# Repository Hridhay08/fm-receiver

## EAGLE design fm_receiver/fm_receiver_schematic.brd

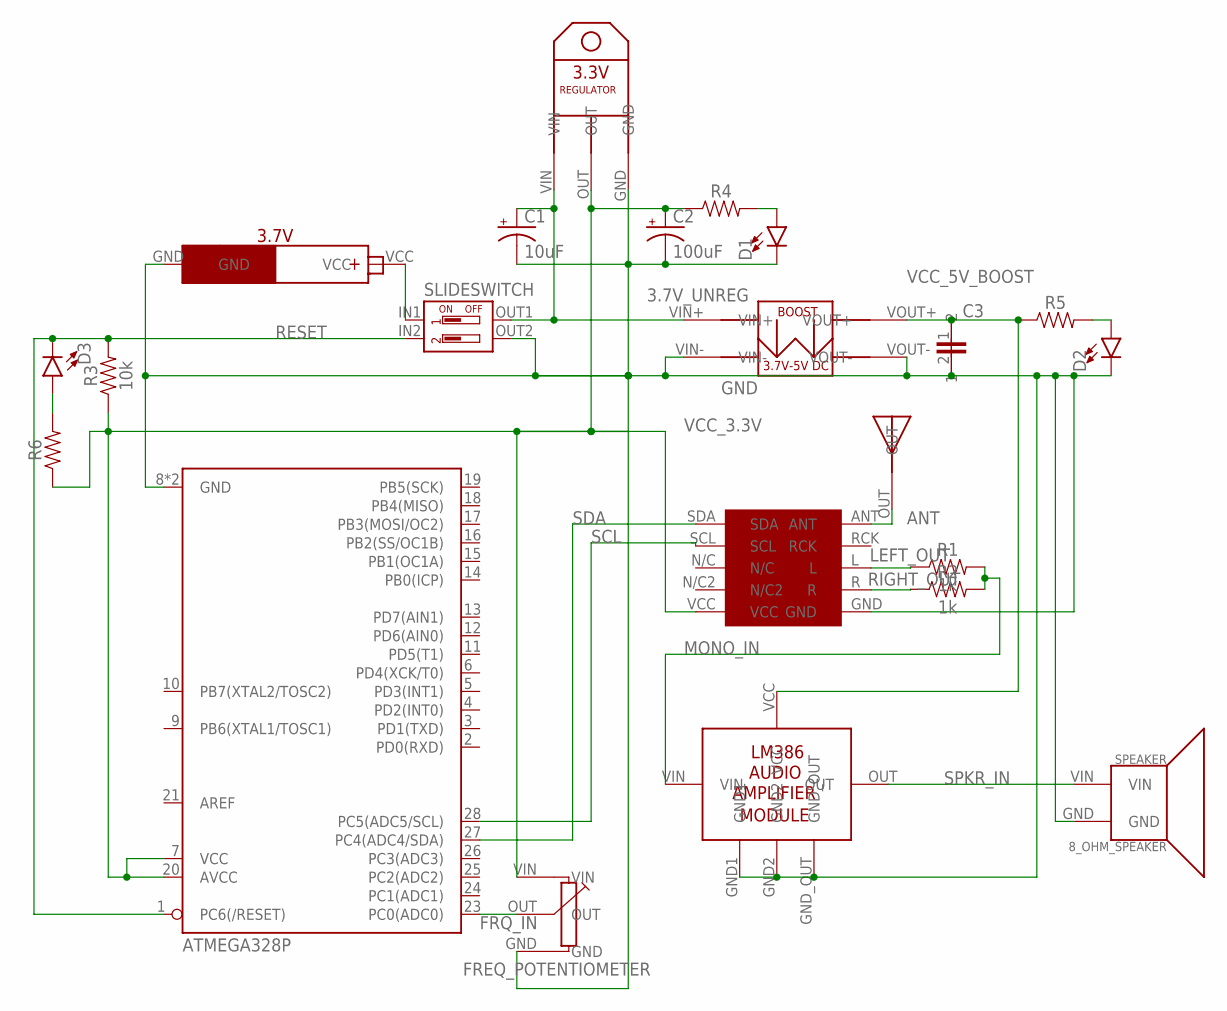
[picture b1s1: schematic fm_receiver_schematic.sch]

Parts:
3.3V_REGULATOR: LDO_REG_3.3V
3.7_5_BOOST: 3.7V_5V_BOOST_CONV
ANTENNA: SIMPLE_ANTENNA
ATMEGA328P: 328P; DIP28
C1: 10uF; CPOL-RADIAL-2.5MM-5MM
C2: 100uF; CPOL-RADIAL-2.5MM-6.5MM
C3: 0.1UF_CER_CAP
D1, D2, D3: LED5MM; LED_5MM
FM_RECEIVER: RDA
FREQ_POTENTIOMETER: POTENTIOMETER_LARGE
LM386_MODULE: LM386_AUDIO_AMP_MODULE
PWR_SUPPLY: 3.7V_PWR_DESIGNATOR
R1, R2: 1k; AXIAL-0.3
R3: 10k; AXIAL-0.3
R4, R5, R6: AXIAL-0.3
SLIDESWITCH: 2_WAY_DIP_PWR_RST_SLIDESWITCH
SPEAKER: 8_OHM_SPEAKER

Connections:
3.7V_UNREG: 3.3V_REGULATOR.VIN, 3.7_5_BOOST.VIN+, C1.1 (+), SLIDESWITCH.OUT1
ANT: ANTENNA.OUT, FM_RECEIVER.ANT
FRQ_IN: ATMEGA328P.23 (PC0(ADC0)), FREQ_POTENTIOMETER.OUT
GND: 3.3V_REGULATOR.GND, 3.7_5_BOOST.VIN-, 3.7_5_BOOST.VOUT-, ATMEGA328P.8 (GND), ATMEGA328P.22 (GND), C1.2 (-), C2.2 (-), C3.2, D1.K (C), D2.K (C), FM_RECEIVER.GND, FREQ_POTENTIOMETER.GND, LM386_MODULE.GND1, LM386_MODULE.GND2, LM386_MODULE.GND_OUT, PWR_SUPPLY.GND, SLIDESWITCH.OUT2, SPEAKER.GND
LEFT_OUT: FM_RECEIVER.L, R1.P$1 (1)
MONO_IN: LM386_MODULE.VIN, R1.P$2 (2), R2.P$2 (2)
unnamed: PWR_SUPPLY.VCC, SLIDESWITCH.IN1
unnamed: D1.A, R4.P$2 (2)
unnamed: D2.A, R5.P$2 (2)
unnamed: D3.A, R6.P$2 (2)
RESET: ATMEGA328P.1 (PC6(/RESET)), D3.K (C), R3.P$2 (2), SLIDESWITCH.IN2
RIGHT_OUT: FM_RECEIVER.R, R2.P$1 (1)
SCL: ATMEGA328P.28 (PC5(ADC5/SCL)), FM_RECEIVER.SCL
SDA: ATMEGA328P.27 (PC4(ADC4/SDA)), FM_RECEIVER.SDA
SPKR_IN: LM386_MODULE.OUT, SPEAKER.VIN
VCC_3.3V: 3.3V_REGULATOR.OUT, ATMEGA328P.7 (VCC), ATMEGA328P.20 (AVCC), C2.1 (+), FM_RECEIVER.VCC, FREQ_POTENTIOMETER.VIN, R3.P$1 (1), R4.P$1 (1), R6.P$1 (1)
VCC_5V_BOOST: 3.7_5_BOOST.VOUT+, C3.1, LM386_MODULE.VCC, R5.P$1 (1)

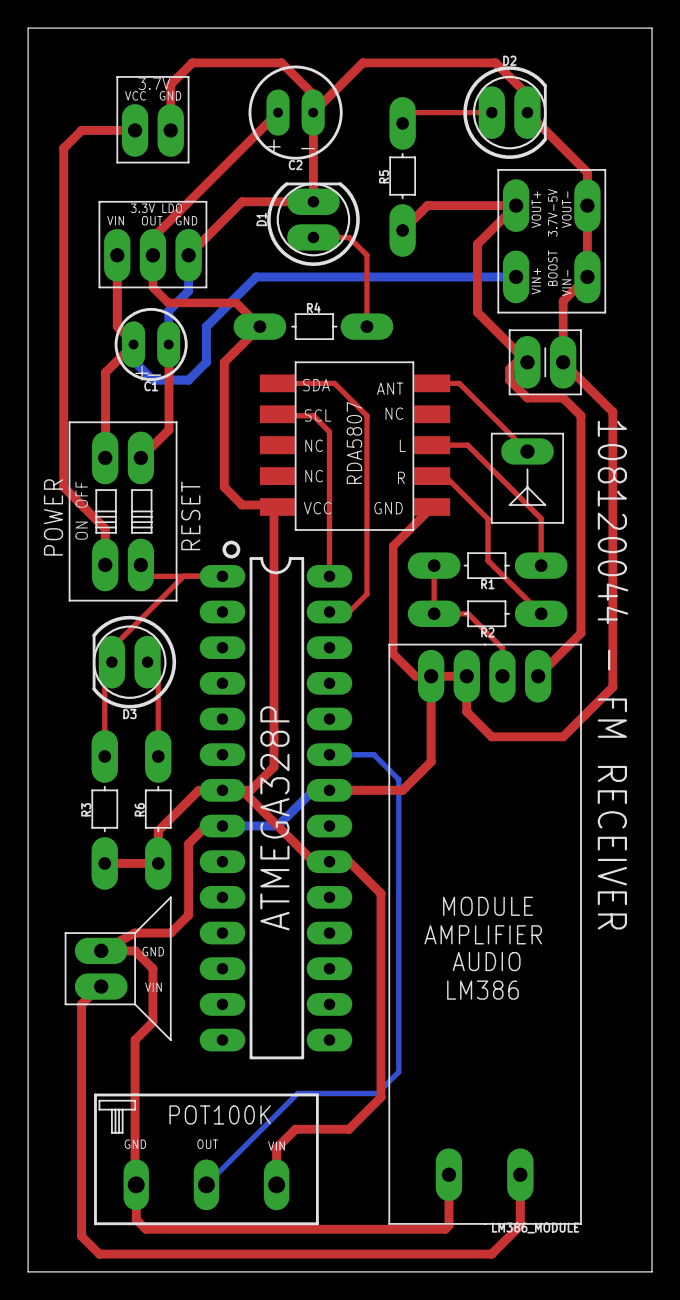
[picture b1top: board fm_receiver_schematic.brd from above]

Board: 2 copper layers, 44.4 x 88.6 mm, 22 parts (0 on the bottom side), 17 nets.

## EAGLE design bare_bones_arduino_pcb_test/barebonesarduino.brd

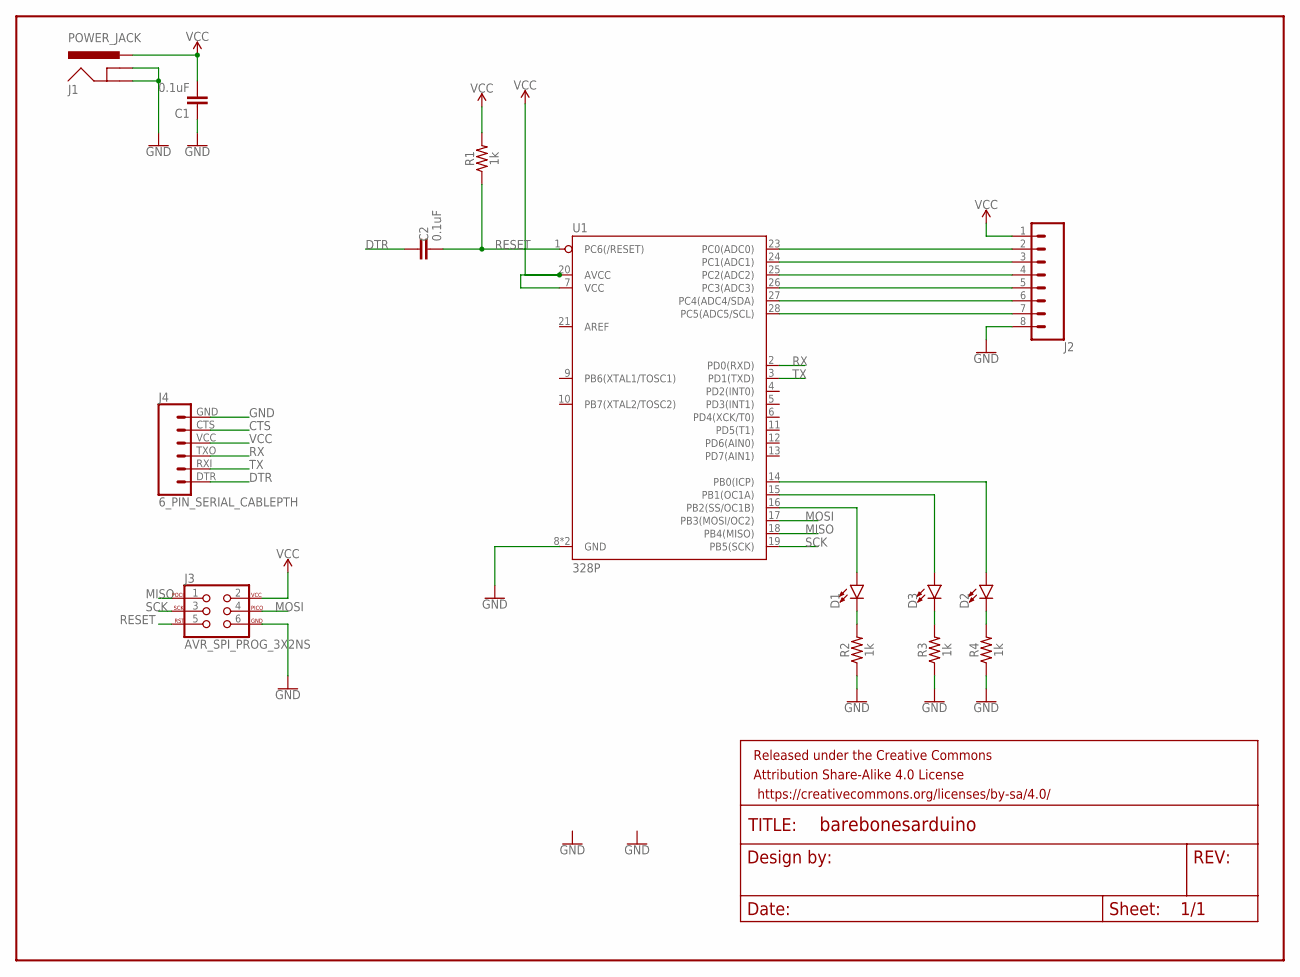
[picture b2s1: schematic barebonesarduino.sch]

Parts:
C1, C2: 0.1uF; CAP-PTH-SMALL-KIT
D1, D2, D3: LED5MM; LED_5MM
FRAME1: FRAME-LETTER; CREATIVE_COMMONS
J1: POWER_JACK; POWER_JACK_PTH
J2: CONN_08"; 1X08
J3: AVR_SPI_PROG_3X2NS; 2X3-NS
J4: 6_PIN_SERIAL_CABLEPTH; FTDI_BASIC
R1, R2, R3, R4: 1k; AXIAL-0.1-KIT
U1: 328P; DIP28

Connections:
CTS: J4.CTS (5)
DTR: C2.1, J4.DTR (1)
GND: C1.1, J1.GND, J1.GNDBREAK, J2.8, J3.6, J4.GND (6), R2.P$1 (1), R3.P$1 (1), R4.P$1 (1), U1.8 (GND), U1.22 (GND)
MISO: J3.1, U1.18 (PB4(MISO))
MOSI: J3.4, U1.17 (PB3(MOSI/OC2))
unnamed: J2.2, U1.23 (PC0(ADC0))
unnamed: D1.A, U1.16 (PB2(SS/OC1B))
unnamed: D3.A, U1.15 (PB1(OC1A))
unnamed: D2.A, U1.14 (PB0(ICP))
unnamed: D1.K (C), R2.P$2 (2)
unnamed: D3.K (C), R3.P$2 (2)
unnamed: D2.K (C), R4.P$2 (2)
unnamed: J2.7, U1.28 (PC5(ADC5/SCL))
unnamed: J2.6, U1.27 (PC4(ADC4/SDA))
unnamed: J2.5, U1.26 (PC3(ADC3))
unnamed: J2.4, U1.25 (PC2(ADC2))
unnamed: J2.3, U1.24 (PC1(ADC1))
RESET: C2.2, J3.5, R1.P$1 (1), U1.1 (PC6(/RESET))
RX: J4.TXO (3), U1.2 (PD0(RXD))
SCK: J3.3, U1.19 (PB5(SCK))
TX: J4.RXI (2), U1.3 (PD1(TXD))
VCC: C1.2, J1.PWR, J2.1, J3.2, J4.VCC (4), R1.P$2 (2), U1.7 (VCC), U1.20 (AVCC)

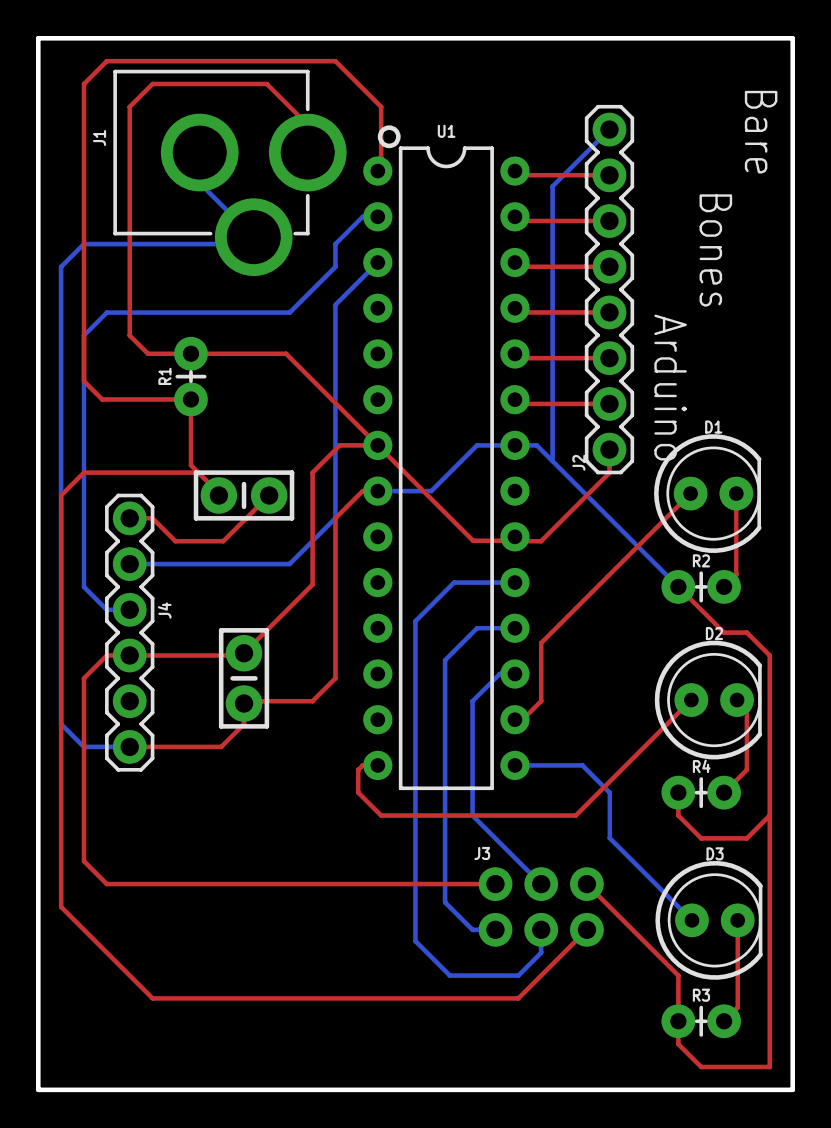
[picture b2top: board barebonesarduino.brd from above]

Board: 2 copper layers, 41.9 x 58.4 mm, 15 parts (0 on the bottom side), 21 nets.

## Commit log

2022-11-19 changed round solder pads to long pads, and rerouted traces accordingly to prevent DRC errors
2022-11-20 modified gerbers to reflect changed solder pads
2022-11-22 connected crucial GND terminal of RDA5807 to GND net, which was previously missed
2022-12-12 generating pcb mask, new code and modified existing code for the atmega program, and other supplementary programs
2022-12-13 physical demonstration media and minor comment removal in a code file
2022-12-15 project report updated
2022-12-15 project report again updated

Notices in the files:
parts and their libraries:
SparkFun-Capacitors: Licensing: Creative Commons ShareAlike 4.0 International - https://creativecommons.org/licenses/by-sa/4.0
SparkFun-Aesthetics: Released under the Creative Commons Attribution Share-Alike 4.0 License
SparkFun-Aesthetics: https://creativecommons.org/licenses/by-sa/4.0
